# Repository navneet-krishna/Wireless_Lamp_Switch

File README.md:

# Wireless Lamp Switch: KiCad 10 project

Two 2-layer boards: a battery-powered **Transmitter** (touch-to-toggle) and a mains-switching **Receiver**.

| File | Purpose |
|---|---|
| `Transmitter.kicad_pro / .kicad_sch / .kicad_pcb` | Transmitter project, schematic, PCB (70 x 85 mm) |
| `Receiver.kicad_pro / .kicad_sch / .kicad_pcb` | Receiver project, schematic, PCB (100 x 90 mm) |
| `Wireless_Lamp_Switch.kicad_sym` | Shared symbol library used by both schematics |
| `Wireless_Lamp_Switch.pretty/` | Custom footprints: `MT3608_Module`, `Relay_Module_1CH` |
| `*.net` | Netlists exported from the schematics and imported into the PCBs |
| `*.kicad_dru` | Custom DRC rules (3 mm mains isolation, 1.5 mm mains edge clearance) |
| `fab/*_gerbers.zip` | Gerbers + Excellon drills + this README, ready for fabrication |
| `fab/*-schematic.pdf`, `fab/*-3d-*.png` | Printable schematics and board renders |
| `reports/` | ERC and DRC reports (all clean, including schematic parity) |
| `tools/` | Generator scripts; `bash tools/build.sh` rebuilds everything |

Open either `.kicad_pro` in KiCad 10. Both projects share the libraries through the local
`sym-lib-table` / `fp-lib-table`.

## Nets

**Transmitter**: BAT+, BAT-, VIN_RAW, +5V, GND, TOUCH_SIG, RF_3V3, RF_CE, RF_CSN, RF_SCK, RF_MOSI, RF_MISO

```
2xAAA (+) -> SW1 -> MT3608 IN+          MT3608 OUT+ -> +5V -> Nano 5V, TTP223 VCC
2xAAA (-) ---------> MT3608 IN-         MT3608 OUT- -> GND
TTP223 OUT -> Nano D3                   Nano 3V3 -> RF_3V3 -> nRF24 VCC (+ C1 10uF)
D8 -> CE   D9 -> CSN   D13 -> SCK   D11 -> MOSI   D12 -> MISO
```

**Receiver**: +5V, GND, RELAY_IN, RF_*, AC_HOT_IN, AC_HOT_OUT, AC_NEUTRAL

```
DC jack +5V -> Nano 5V, Relay VCC        DC jack GND -> GND
Nano D7 -> RELAY_IN -> Relay IN          Nano 3V3 -> RF_3V3 -> nRF24 VCC (+ C1 10uF)
AC IN HOT -> Relay COM ; Relay NO -> AC OUT HOT ; AC IN NEUTRAL -> AC OUT NEUTRAL
```

## Board layout

**Transmitter**: nRF24L01 on the top edge with a copper keep-out under the antenna. Nano in
the centre, USB facing the right edge. TTP223 on the left (front) edge. MT3608 along the bottom,
with the power switch and battery connector next to its input pads. SPI is routed as a short
parallel bundle around the Nano's USB end. Both layers are poured with GND and stitched with vias.

**Receiver**: low-voltage section on the left and mains section on the right. Between them are
a 1.5 mm milled slot and a silkscreen isolation barrier. The nRF24 sits in the top-left corner,
as far as possible from the relay and mains. The DC jack is on the left edge, opposite the AC
terminals. Mains nets use 2.5 mm traces with at least 3 mm clearance, enforced by the `AC` net
class and `Receiver.kicad_dru`. HOT runs only through relay COM to NO. NEUTRAL goes straight
from terminal to terminal. The GND pour stops 3.8 mm before the barrier.

## Bill of materials

| Ref | Part | Footprint |
|---|---|---|
| A1 | Arduino Nano v3 (both boards) | 2x15 2.54 mm headers (`Module:Arduino_Nano`) |
| U1 | nRF24L01+ module (both boards) | 2x4 2.54 mm header |
| C1 | 10 uF 16 V electrolytic (both boards) | 5 mm radial |
| U2 | TTP223 touch module (TX) | 1x3 2.54 mm header (GND, OUT, VCC) |
| U3 | MT3608 boost module (TX) | 4 pads (IN+, IN-, OUT+, OUT-) |
| SW1 | SPST slide switch (TX) | 2.54 mm slide switch |
| BT1 | 2xAAA holder with JST-PH lead (TX) | JST-PH 2-pin |
| K1 | 5 V 1-channel relay module (RX) | 3-pin header + NO/COM/NC jumper pads |
| J1 | 5 V barrel jack, centre positive (RX) | CUI PJ-063AH |
| J2, J3 | 2-pin screw terminal, 7.5 mm pitch, 300 V (RX) | Metz Type175 |
| H1-H4 | M3 mounting holes | NPTH 3.2 mm |

## Assembly

1. **Before soldering the MT3608, set its output to 5.0 V.** Power it from the batteries, then
   adjust the trimmer while measuring OUT+. Most modules ship at a higher voltage, and anything
   above 5.5 V on the Nano 5V pin will damage it.
2. Solder female headers for the Nano, nRF24 and TTP223 so the modules can be removed.
3. Fit the relay module's 3-pin header into K1 VCC/GND/IN. Connect its screw-terminal COM, NO
   and NC to the K1 COM/NO/NC pads with short 18 AWG solid jumpers. The pads are spaced 6 mm apart.
4. Use only the 7.5 mm mains-rated terminals for AC wiring. Fit the receiver in a closed,
   non-conductive enclosure with strain relief. The milled slot must stay free of debris.
5. Check that the relay module's own contact rating covers the lamp load.

## Safety

The receiver switches mains voltage. Never connect mains while USB is plugged into the Nano,
and never touch the board while it is powered. If you are not qualified to build mains
equipment, have the AC section checked by someone who is.

## Changes from the original spec

- **C1 (10 uF) was added on both boards.** The Nano's 3V3 pin cannot supply the nRF24's
  current peaks without bulk capacitance.
- **AC_NEUTRAL and AC_NEUTRAL_OUT are a single net.** They are joined directly, so KiCad can
  give them only one name. Both terminals are still labelled NEUTRAL on the silkscreen.
- **BAT- and GND are separate nets on the board.** They only join inside the MT3608, whose IN-
  and OUT- are common.
- **Schematic files use the `.kicad_sch` extension.** This is the KiCad 6-10 format; `.sch` is
  the pre-KiCad-6 format.

## Fabrication

Upload `fab/Transmitter_gerbers.zip` and `fab/Receiver_gerbers.zip` to any standard fab house:
2 layers, 1.6 mm FR-4, 1 oz copper, HASL, any mask colour. The receiver has an internal milled
slot (1.5 x 49 mm) on Edge.Cuts, which every common fab supports.

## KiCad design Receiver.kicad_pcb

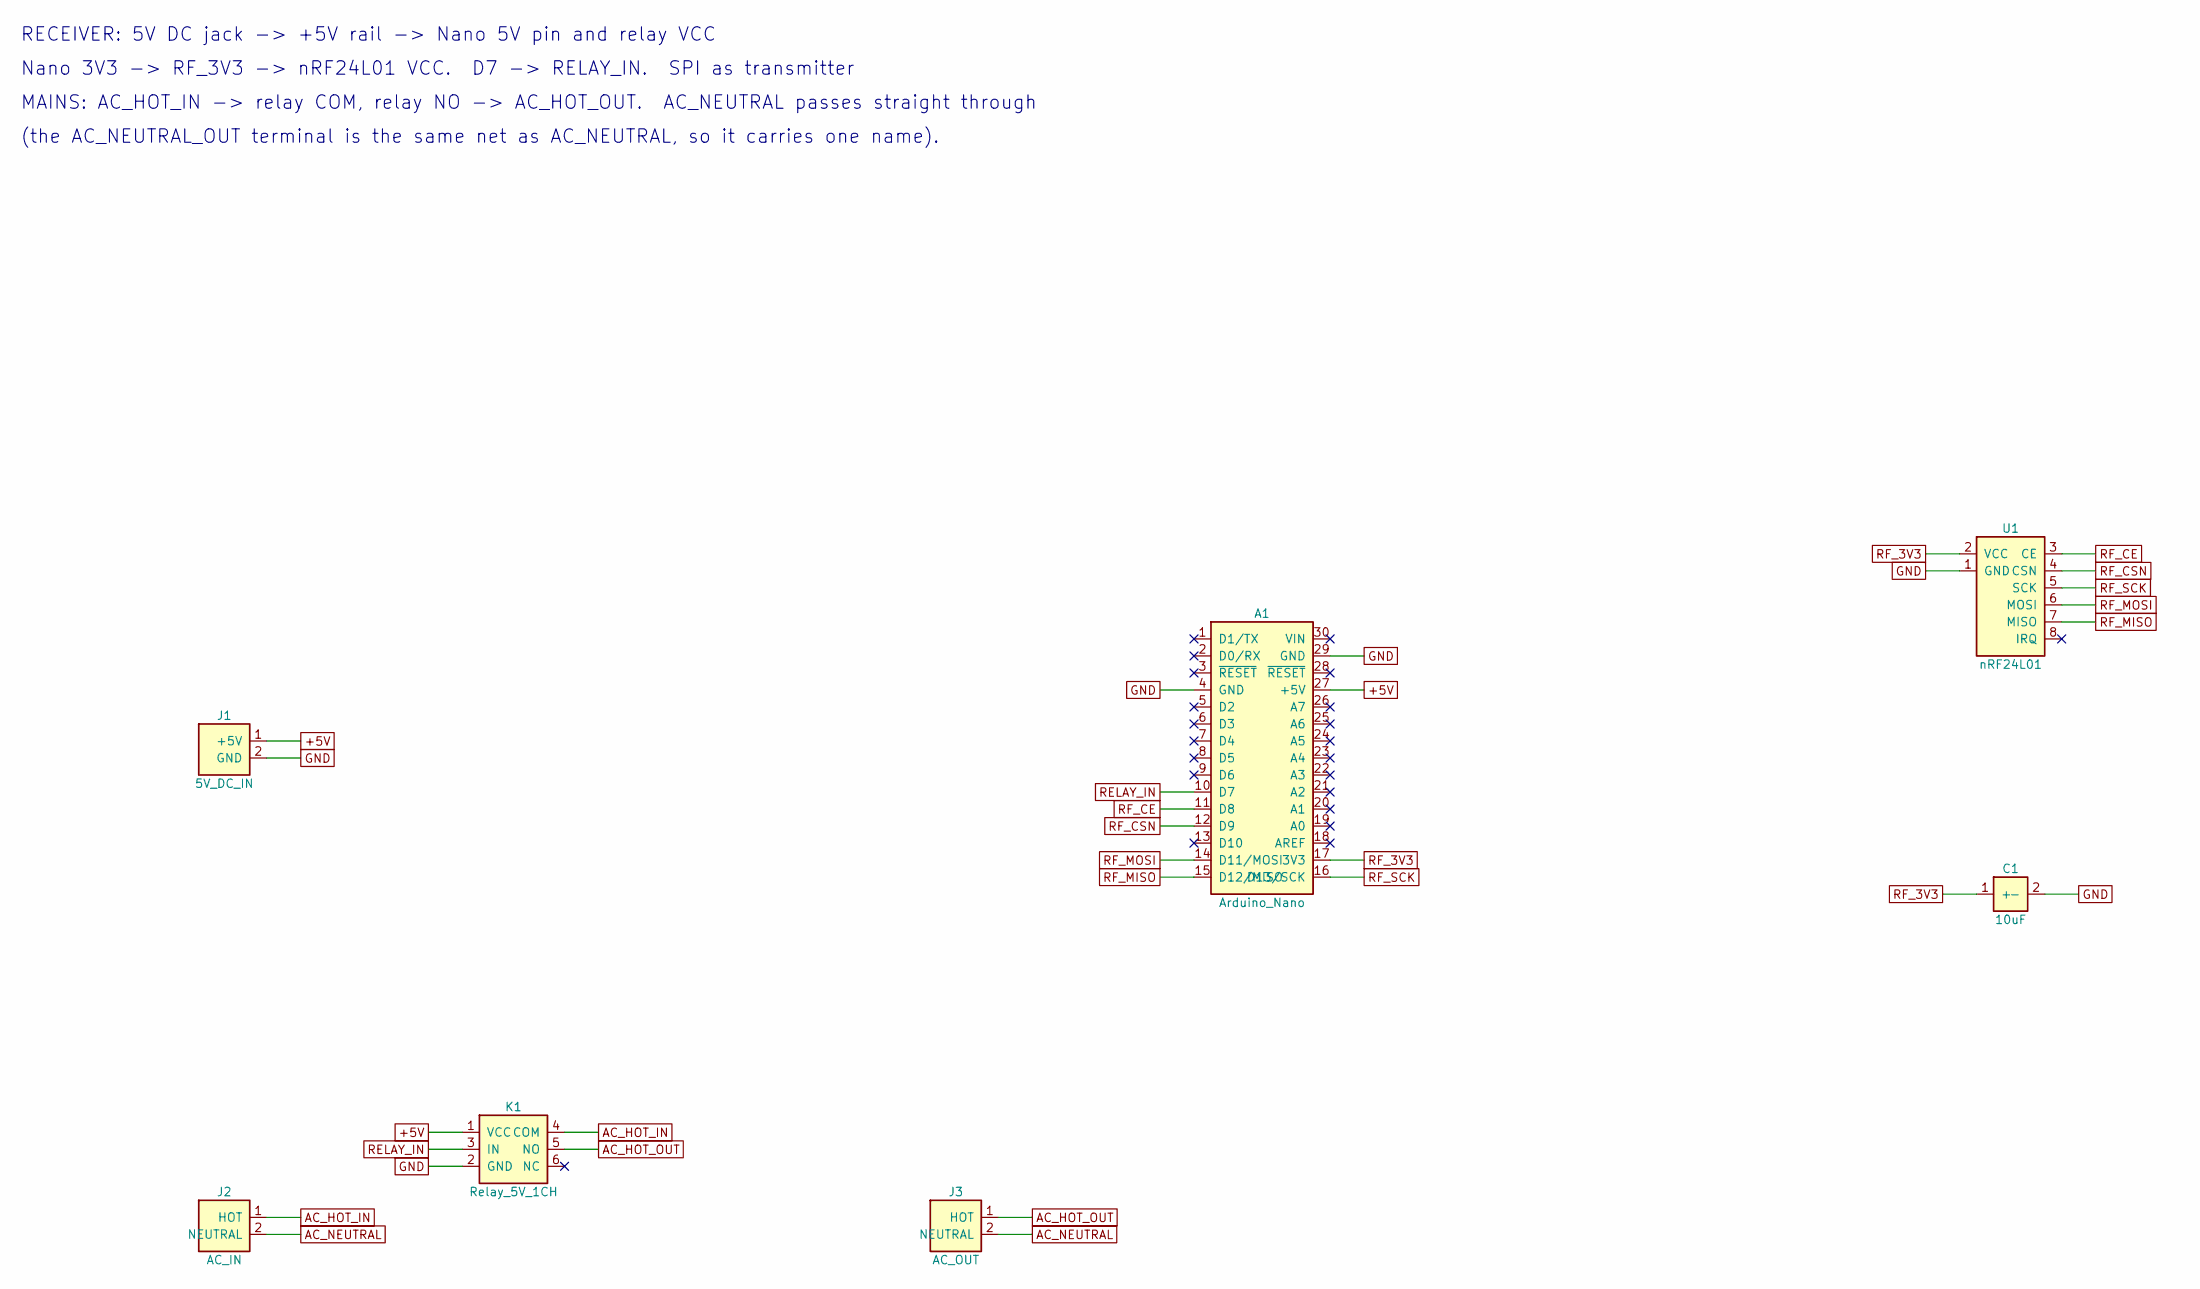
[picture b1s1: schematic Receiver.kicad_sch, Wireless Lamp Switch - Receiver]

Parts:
A1: Arduino_Nano
C1: 10uF; CP_Radial_D5.0mm_P2.00mm
J1: 5V_DC_IN; BarrelJack_CUI_PJ-063AH_Horizontal
J2: AC_IN; TerminalBlock_MetzConnect_Type175_RT02702HBLC_1x02_P7.50mm_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
J3: AC_OUT; TerminalBlock_MetzConnect_Type175_RT02702HBLC_1x02_P7.50mm_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
K1: Relay_5V_1CH; Relay_Module_1CH
U1: nRF24L01; PinHeader_2x04_P2.54mm_Vertical

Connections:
+5V: A1.27 (+5V), J1.1 (+5V), K1.1 (VCC)
AC_HOT_IN: J2.1 (HOT), K1.4 (COM)
AC_HOT_OUT: J3.1 (HOT), K1.5 (NO)
AC_NEUTRAL: J2.2 (NEUTRAL), J3.2 (NEUTRAL)
GND: A1.4 (GND), A1.29 (GND), C1.2 (-), J1.2 (GND), K1.2 (GND), U1.1 (GND)
RELAY_IN: A1.10 (D7), K1.3 (IN)
RF_3V3: A1.17 (3V3), C1.1 (+), U1.2 (VCC)
RF_CE: A1.11 (D8), U1.3 (CE)
RF_CSN: A1.12 (D9), U1.4 (CSN)
RF_MISO: A1.15 (D12/MISO), U1.7 (MISO)
RF_MOSI: A1.14 (D11/MOSI), U1.6 (MOSI)
RF_SCK: A1.16 (D13/SCK), U1.5 (SCK)

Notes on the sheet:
(the AC_NEUTRAL_OUT terminal is the same net as AC_NEUTRAL, so it carries one name).
Nano 3V3 -> RF_3V3 -> nRF24L01 VCC. D7 -> RELAY_IN. SPI as transmitter
RECEIVER: 5V DC jack -> +5V rail -> Nano 5V pin and relay VCC
MAINS: AC_HOT_IN -> relay COM, relay NO -> AC_HOT_OUT. AC_NEUTRAL passes straight through

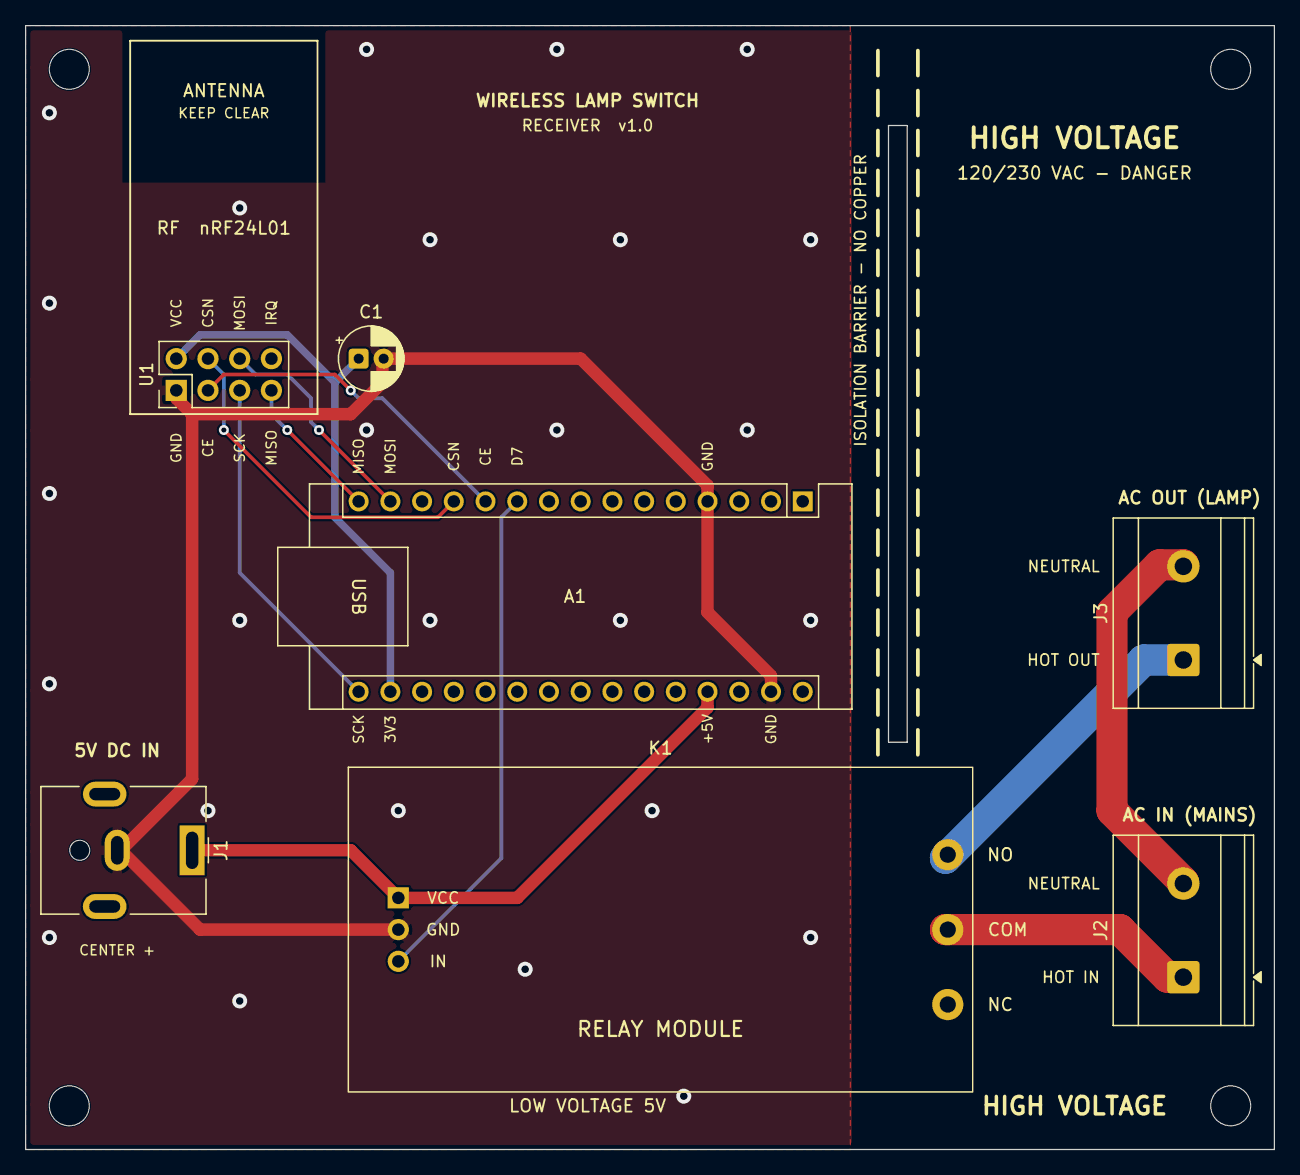
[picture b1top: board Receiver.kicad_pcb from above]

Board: 2 copper layers, 100.0 x 90.0 mm, 11 parts (0 on the bottom side), 12 nets.

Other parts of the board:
H1, H2, H3, H4: M3; MountingHole_3.2mm_M3
